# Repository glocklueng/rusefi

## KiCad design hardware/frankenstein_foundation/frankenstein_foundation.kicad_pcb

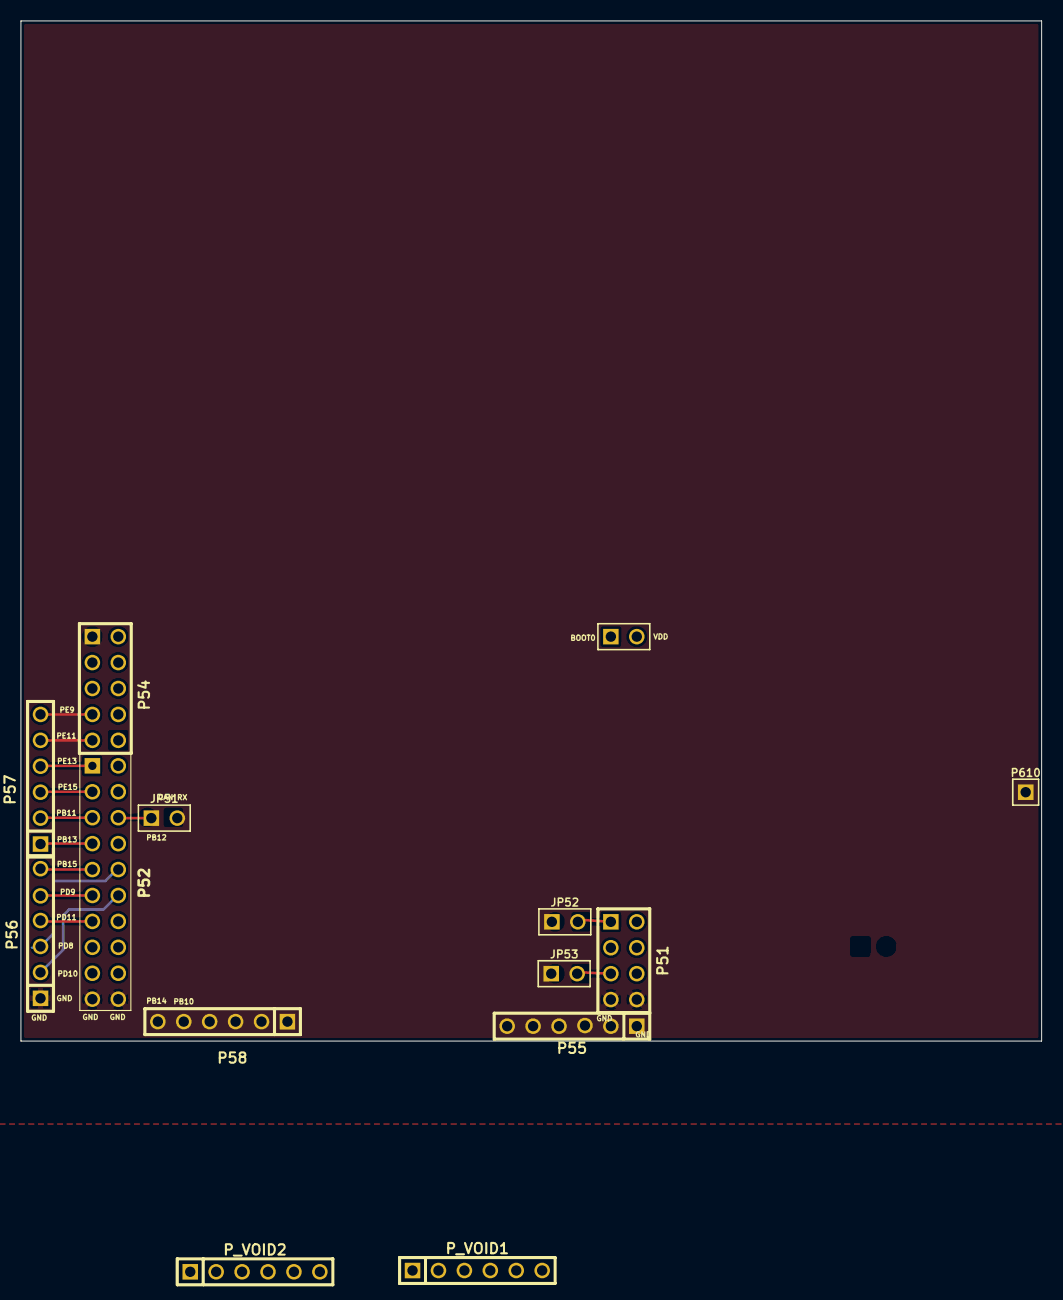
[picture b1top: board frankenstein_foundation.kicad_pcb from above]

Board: 2 copper layers, 100.0 x 99.9 mm, 14 parts (0 on the bottom side), 27 nets.

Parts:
JP51, JP52, JP53: JUMPER; PIN_ARRAY_2_A
P51: CONN_4X2; pin_array_4x2
P52: CONN_10X2; PIN_ARRAY_10X2_M
P53: CONN_2; PIN_ARRAY_2X1
P54: CONN_5X2; PIN_ARRAY_5x2
P55, P56, P57, P58: CONN_6; PIN_ARRAY-6X1
P610: CONN_1; PIN_ARRAY_1
P_VOID1, P_VOID2: CONN_6; PIN_ARRAY-6X1

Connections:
/CAM: JP53.1, P_VOID1.6
/CAN_RX: JP51.2, P_VOID1.5
/CRANK: JP52.1, P_VOID1.4
/H_IN1: P54.8, P_VOID2.6
/H_IN2: P54.10, P_VOID2.5
/H_IN3: P54.6, P_VOID2.3
/H_IN4: P52.2, P_VOID2.4
/H_IN5: P51.6, P55.2
/H_IN6: P51.4, P55.3
/PA8: JP52.2, P51.1
/PB10: P52.4, P58.5
/PB11: P52.5, P57.2
/PB12: JP51.1, P52.6
/PB13: P52.7, P57.1
/PB14: P52.8, P58.6
/PB15: P52.9, P56.6
/PC6: JP53.2, P51.5
/PD8: P52.10, P56.3
/PD9: P52.11, P56.5
/PD10: P52.12, P56.2
/PD11: P52.13, P56.4
/PE9: P54.7, P57.6
/PE11: P54.9, P57.5
/PE13: P52.1, P57.4
/PE15: P52.3, P57.3
/VP: P610.1, P_VOID1.3
GND: P51.7, P51.8, P52.19, P52.20, P55.1, P55.4, P55.5, P55.6, P56.1, P58.1, P58.2, P58.3, P58.4

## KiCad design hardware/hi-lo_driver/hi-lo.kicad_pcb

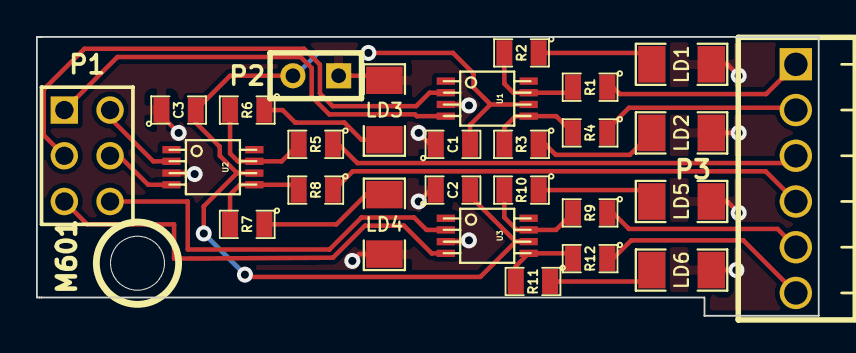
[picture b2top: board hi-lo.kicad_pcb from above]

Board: 2 copper layers, 43.4 x 15.5 mm, 29 parts (1 on the bottom side), 26 nets.

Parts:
C1, C2, C3: 0.1uF; SM0805
G1: LOGO
LD1, LD2, LD3, LD4, LD5, LD6: LED; SM1206
M601: CONN_1; 1pin
P1: CONN_3X2; pin_array_3x2
P2: CONN_2; SIL-2
P3: CONN_6; OSTVN06A150
R1, R4, R5, R8, R9, R12: 100; SM0805
R2, R3, R6, R7, R10, R11: 2700; SM0805
U1, U2, U3: TC4427AVOA; msoic-8

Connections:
/HL1: P3.1, R1.1
/HL2: P3.2, R4.1
/HL3: P3.3, R5.1
/HL4: P3.4, R8.1
/HL5: P3.5, R9.1
/HL6: P3.6, R12.1
/H_IN1: P1.1, U1.4
/H_IN2: P1.2, U2.2
/H_IN3: P1.3, U1.2
/H_IN4: P1.4, U2.4
/H_IN5: P1.5, U3.4
/H_IN6: P1.6, U3.2
/VP: C1.2, C2.2, C3.2, P2.2, U1.6, U2.6, U3.6
GND: C1.1, C2.1, C3.1, LD1.2, LD2.2, LD3.2, LD4.2, LD5.2, LD6.2, P2.1, U1.3, U2.3, U3.3
unnamed: LD5.1, R10.1
unnamed: LD2.1, R3.1
unnamed: R3.2, R4.2, U1.5
unnamed: R7.2, R8.2, U2.5
unnamed: LD3.1, R6.1
unnamed: R5.2, R6.2, U2.7
unnamed: LD1.1, R2.1
unnamed: R1.2, R2.2, U1.7
unnamed: LD4.1, R7.1
unnamed: LD6.1, R11.1
unnamed: R9.2, R10.2, U3.7
unnamed: R11.2, R12.2, U3.5

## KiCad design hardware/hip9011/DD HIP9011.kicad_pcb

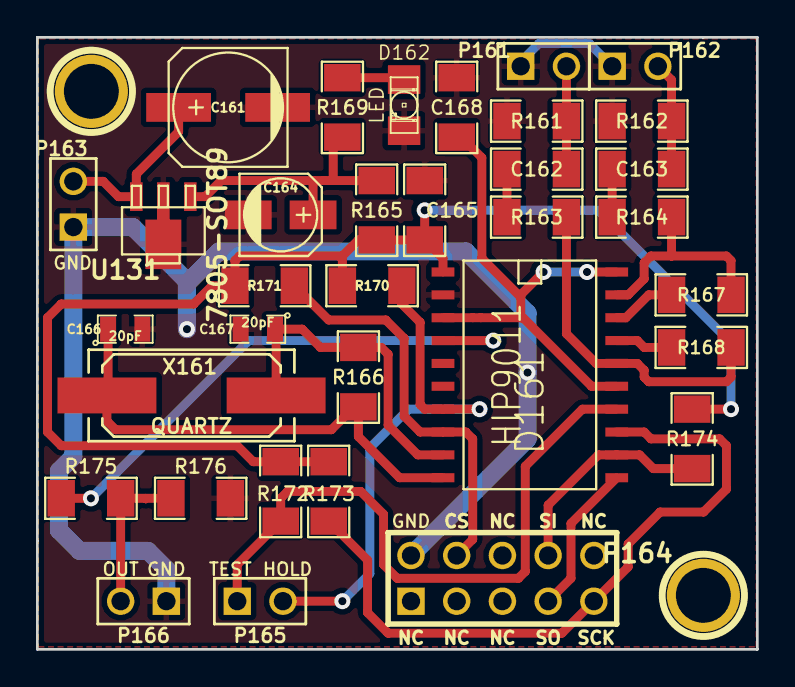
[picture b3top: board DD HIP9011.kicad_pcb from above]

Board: 2 copper layers, 40.0 x 34.0 mm, 35 parts (1 on the bottom side), 24 nets.

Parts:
C161: 100u; c_elec_6.3x5.3
C162, C163: 47n; SM1206
C164: 10u; c_elec_4x5.3
C165: 100n; SM1206
C166, C167: 20pF; SM0805
C168: 22n; SM1206
D161: HIP9011; SO20L
D162: LED; LED-1206
G161: LOGO; LOGO_F
P161: KNOCK 1; PIN_ARRAY_2X1
P162: KNOCK 2; PIN_ARRAY_2X1
P163: 12V; PIN_ARRAY_2X1
P164: CONN_5X2; PIN_ARRAY_5x2
P165, P166: CONN_2; PIN_ARRAY_2X1
R161, R162, R166: 1M; SM1206
R163, R164, R175, R176: 10k; SM1206
R165: 10R; SM1206
R167, R168: 68k; SM1206
R169: 470R; SM1206
R170, R171, R172, R173, R174: 1K; SM1206
U131: 7805-SOT89; sot89
X161: QUARTZ; Q_49U3HMS

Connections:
/+5V: C165.1, D161.1, R165.2, R170.1, R171.1, R172.1, R173.1, R174.1
/+12V: C161.1, P163.2, U131.3
/CS: D161.8, P164.4, R171.2
/GND: C161.2, C164.2, C165.2, C166.2, C167.2, C168.2, D161.2, D162.2, P161.1, P162.1, P163.1, P164.2, P166.1, R161.2, R162.2, R176.2, U131.2
/INT/HLD: D161.7, P165.2, R170.2
/INTOUT: D161.4, R175.1
/OUT: P166.2, R175.2, R176.1
/SCK: D161.13, P164.9, R173.2
/SI: D161.12, P164.8, R174.2
/SO: D161.11, P164.7
/TEST: D161.14, P165.1, R172.2
unnamed: D162.1, R169.1
unnamed: C164.1, R165.1, R169.2, U131.1
unnamed: C167.1, D161.9, R166.2, X161.2
unnamed: C163.1, P162.2, R162.1
unnamed: C163.2, R164.1
unnamed: C166.1, D161.10, R166.1, X161.1
unnamed: C168.1, D161.3, D161.15, D161.20
unnamed: D161.16, R163.2, R168.2
unnamed: D161.17, R168.1
unnamed: D161.18, R167.1
unnamed: D161.19, R164.2, R167.2
unnamed: C162.2, R163.1
unnamed: C162.1, P161.2, R161.1

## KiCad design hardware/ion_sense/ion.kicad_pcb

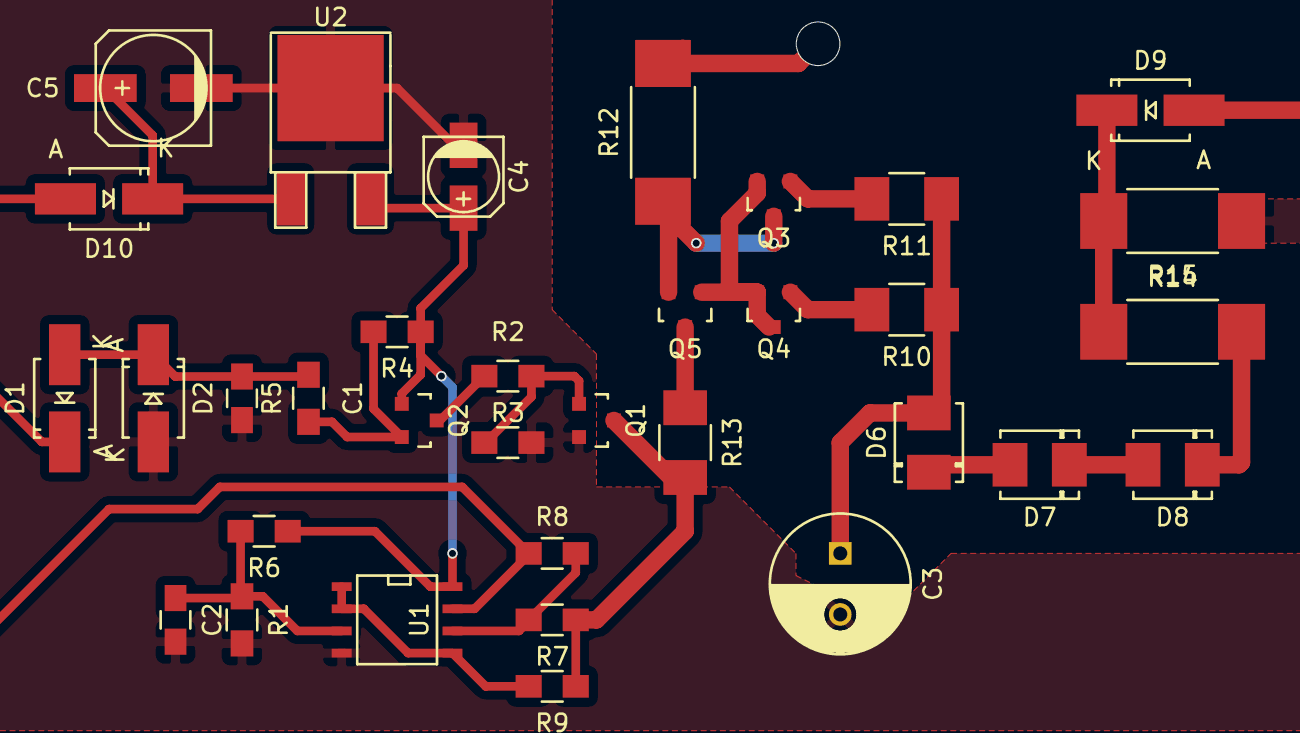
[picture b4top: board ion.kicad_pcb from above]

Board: 2 copper layers, 40 parts (0 on the bottom side), 25 nets.

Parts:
C1: 0.1uF; C_0805_HandSoldering
C2: 1uF; C_0805_HandSoldering
C3: 2.2uF 350V; C_Radial_D8_L11.5_P3.5
C4: 4.7uF 16V; c_elec_4x4.5
C5: 47uF 25V; c_elec_6.3x4.5
D1, D2, D9, D10: US1M; SMA_Handsoldering
D6, D7, D8: 1N4740A; DO-214BA
P0, P1, P2, P3, P4, P5: CONN_01X01; MountingHole_2-5mm
Q1: MMBT3904; SOT-23
Q2, Q3, Q4, Q5: MPSA92; SOT-23
R1, R6, R7, R8: 51k; R_0805_HandSoldering
R2: 2k; R_0805_HandSoldering
R3: 3.9k; R_0805_HandSoldering
R4: 10k; R_0805_HandSoldering
R5: 1k; R_0805_HandSoldering
R9: 4.7k; R_0805_HandSoldering
R10, R11: 560; R_1210_HandSoldering
R12: 180k; R_2512_HandSoldering
R13: 68k; R_1210_HandSoldering
R14: 33k; R_2512_HandSoldering
R15: 1M; R_2512_HandSoldering
U1: LM2904; SOIC-8-N
U2: MC78M05CDT; TO-252-2Lead

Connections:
Earth: C1.2, C2.2, C3.2, C4.2, C5.2, D2.2, P5.1, Q1.2, R1.2, R2.2, R15.1, U1.4, U2.2
unnamed: C1.1, D1.2, D2.1, R5.2
unnamed: C2.1, R1.1, R6.2, U1.3
unnamed: C3.1, D6.2, R10.1, R11.1
unnamed: C4.1, Q2.1, R4.1, R6.1, U1.8, U2.3
unnamed: C5.1, D10.1, U2.1
unnamed: D1.1, P0.1
unnamed: D6.1, D7.2
unnamed: D7.1, D8.2
unnamed: D8.1, R14.2
unnamed: D9.1, R14.1, R15.2
unnamed: D9.2, P4.1
unnamed: D10.2, P1.1
unnamed: P3.1, R8.1, U1.7
unnamed: Q1.1, R2.1, R3.1
unnamed: Q1.3, R7.1, R9.1, R13.2
unnamed: Q2.2, R4.2, R5.1
unnamed: Q2.3, R3.2
unnamed: Q3.1, R11.2
unnamed: Q3.2, Q4.2, Q4.3, Q5.1
unnamed: Q3.3, Q5.2, R12.1
unnamed: Q4.1, R10.2
unnamed: Q5.3, R13.1
unnamed: R7.2, R8.2, U1.6
unnamed: R9.2, U1.1, U1.2, U1.5

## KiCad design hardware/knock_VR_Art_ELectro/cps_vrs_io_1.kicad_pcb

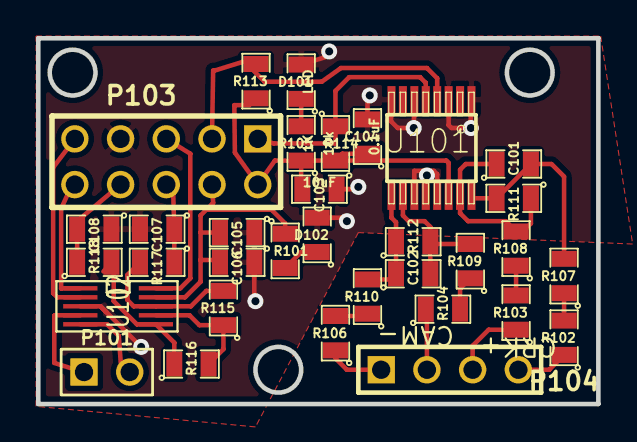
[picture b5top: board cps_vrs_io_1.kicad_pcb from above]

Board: 2 copper layers, 31.1 x 20.3 mm, 34 parts (1 on the bottom side), 29 nets.

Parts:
C101, C102, C108: 1000pF; SM0805
C103: 10uF; SM0805
C104, C106, C107: 0.1uF; SM0805
C105: 1uF; SM0805
D101, D102: LED; SM0805
G101: LOGO; LOGO_F
P101: CONN_2; PIN_ARRAY_2_A
P103: CONN_5X2; PIN_ARRAY_5x2
P104: CONN_4; PIN_ARRAY_4x1
R101, R105: 1K; SM0805
R102, R103, R104, R106, R107, R108, R109, R110, R111, R112: 5k; SM0805
R113, R114: 10k; SM0805
R115, R116: 10K; SM0805
R117, R118: 20K; SM0805
U101: MAX9926/9927; maxim-10-QSOP16
U102: MAX9939; uMAX-uSOP_10

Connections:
/5V: C103.2, C104.1, P103.2, R105.1, R113.1, R114.2, U101.14
/5v stab: C105.2, C106.2, P103.4, R101.1, U102.9
/CAM: P103.1, R114.1, U101.5
/CAM+: P104.1, R106.1
/CAM-: P104.2, R104.1
/CRANK: P103.3, R113.2, U101.4
/CRK2+: P104.4, R102.1
/CRK2-: P104.3, R103.1
/CS-KN1: P103.5, U102.10
/MISO: P103.9, U102.2
/SCK: P103.10, U102.1
/knock1+: C107.1, P103.6, R117.1
/knock1-: C108.2, P103.8, R118.1
/knock_1+p: P101.2, U102.5
/knock_1-p: P101.1, U102.4
GND: C103.1, C104.2, C105.1, C106.1, C107.2, C108.1, D101.2, D102.2, P103.7, U101.1, U101.3, U101.6, U101.8, U101.11, U101.12, U101.13, U102.3
unnamed: R115.1, R116.2, U102.7
unnamed: R115.2, R117.2, U102.8
unnamed: R116.1, R118.2, U102.6
unnamed: D101.1, R105.2
unnamed: D102.1, R101.2
unnamed: R102.2, R107.1
unnamed: R104.2, R109.1
unnamed: R106.2, R110.1
unnamed: R103.2, R108.1
unnamed: C101.1, R108.2, R111.1, U101.15
unnamed: C101.2, R107.2, R111.2, U101.16
unnamed: C102.1, R110.2, R112.1, U101.9
unnamed: C102.2, R109.2, R112.2, U101.10

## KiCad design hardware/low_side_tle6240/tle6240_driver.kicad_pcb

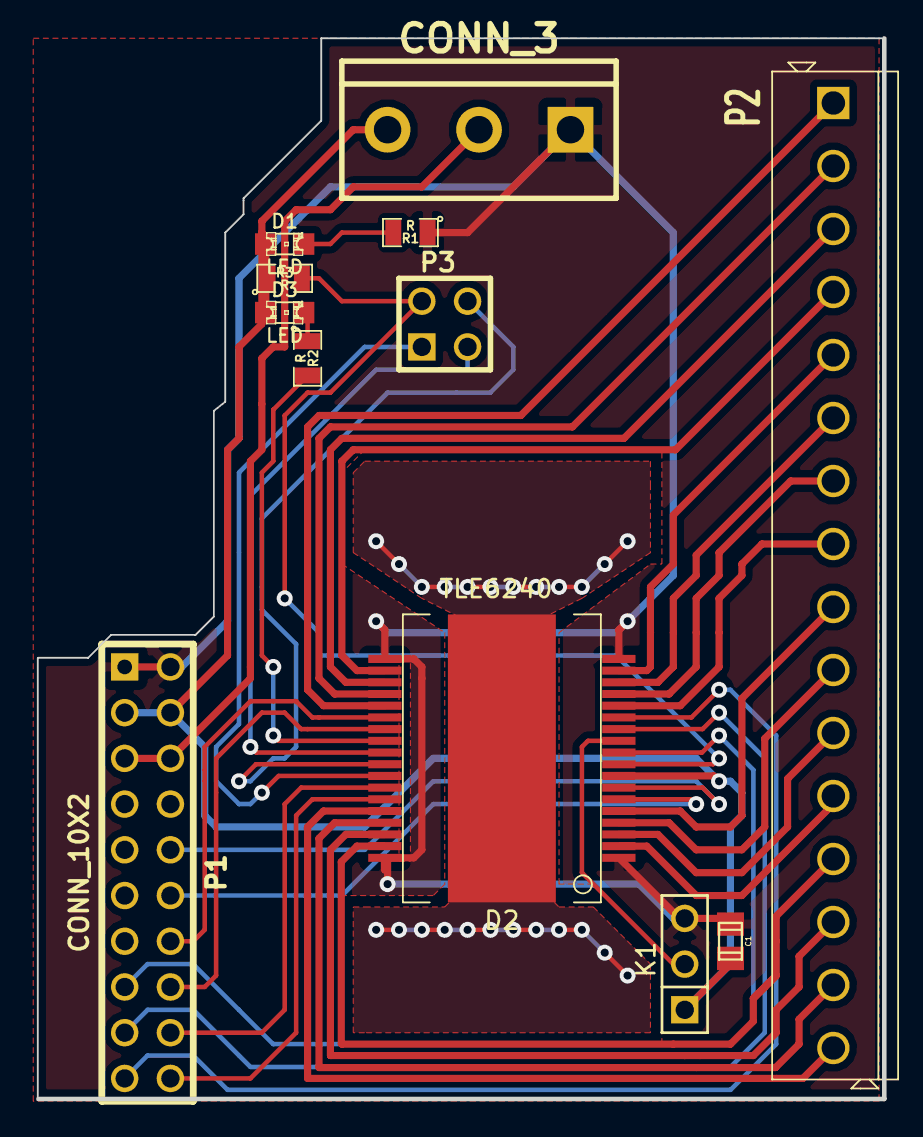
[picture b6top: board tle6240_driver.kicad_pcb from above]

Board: 2 copper layers, 47.0 x 58.9 mm, 12 parts (0 on the bottom side), 36 nets.

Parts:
C1: C; c_0805
D1, D3: LED; LED-0805
D2: TLE6240; PG-DSO-36
K1: CONN_3; PIN_ARRAY_3X1
K2: CONN_3; bornier3
P1: CONN_10X2; PIN_ARRAY_10X2
P2: CONN_16; SIL-16_3.5MM
P3: CONN_2X2; PIN_ARRAY_2X2
R1, R2, R3: R; SM0805

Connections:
+5V: C1.1, D1.1, D2.8, D3.1, K1.1, K2.3, P1.3, P1.4, R3.1
/+3.3V: K2.2, P1.5, P1.6
/CS: D2.10, P1.15
/Fault: D2.26, R2.2
/IN1: D2.6, P1.12
/IN2: D2.7, P1.10
/IN3: D2.12, P1.17
/IN4: D2.13, P1.19
/IN9: D2.24, P1.14
/IN10: D2.25, P1.16
/IN11: D2.30, P1.18
/IN12: D2.31, P1.20
/OUT1: D2.4, P2.10
/OUT2: D2.5, P2.9
/OUT3: D2.14, P2.8
/OUT4: D2.15, P2.7
/OUT5: D2.22, P2.2
/OUT6: D2.23, P2.1
/OUT7: D2.32, P2.16
/OUT8: D2.33, P2.15
/OUT9: D2.2, P2.12
/OUT10: D2.3, P2.11
/OUT11: D2.16, P2.6
/OUT12: D2.17, P2.5
/OUT13: D2.20, P2.4
/OUT14: D2.21, P2.3
/OUT15: D2.34, P2.14
/OUT16: D2.35, P2.13
/PRG: D2.11, K1.2
/Reset: D2.9, P3.2, R3.2
/SCLK: D2.28, P3.4
/SI: D2.29, P3.1
/SO: D2.27, P3.3
GND: C1.2, D2.1, D2.18, D2.19, D2.36, K1.3, K2.1, P1.1, P1.2, R1.1
unnamed: D3.2, R2.1
unnamed: D1.2, R1.2

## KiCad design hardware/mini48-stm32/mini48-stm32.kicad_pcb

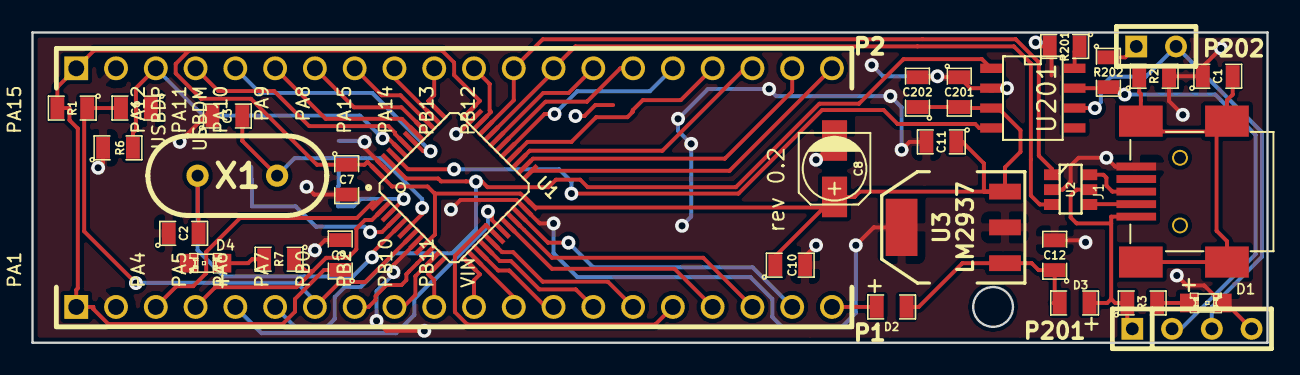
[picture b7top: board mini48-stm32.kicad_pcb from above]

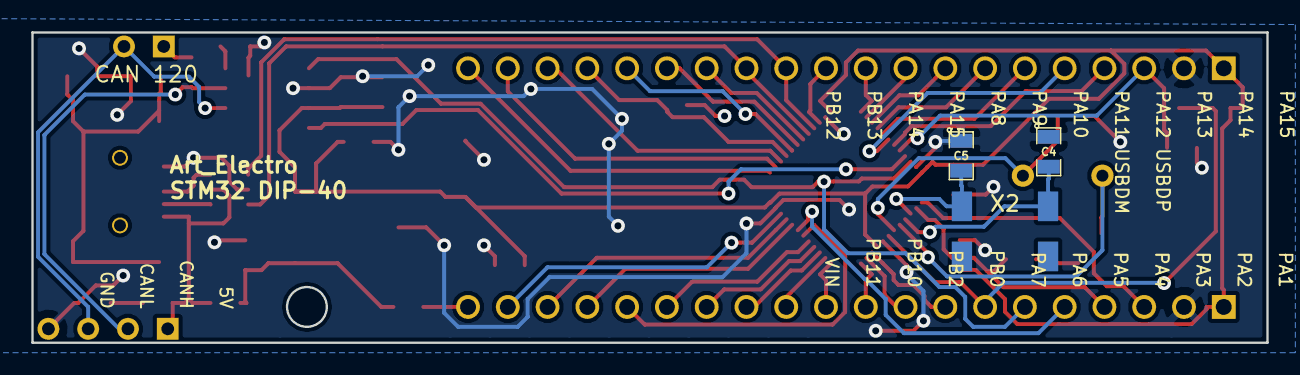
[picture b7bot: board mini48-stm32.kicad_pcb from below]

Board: 2 copper layers, 78.9 x 19.8 mm, 36 parts (3 on the bottom side), 54 nets.

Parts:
C1: 4700pF; SM0805
C2, C3, C4, C5: 18pF; SM0805
C6: 100nF; SM0805
C7, C10, C11: 1uF; SM0805
C8: 47uF; CP_elec_4x5.3
C9, C201: 0.1uF; SM0805
C12: 10uF; SM0805
C202: 4.7uF; SM0805
D1: GREEN; LED-0805_A
D2, D3: DIODESCH; SM0805-diode
D4: BLUE; LED-0805_A
J1: MINI-USB; MINI-USB-5P-3400020P1
P1, P2: CONN_20; PIN_ARRAY_20X1
P201: CONN_4; SIL-4
P202: JUMPER; JUMPER-2
R1, R3, R7: 1k; SM0805
R2: 1M; SM0805
R6, R201: 10k; SM0805
R202: 120; SM0805
U1: STM32F103C8; lqfp48
U2: NUF2101MT1G; SOT-457
U3: LM2937; SOT223
U201: SN65HVD230; SO8E
X1: 8MHz; HC-49V
X2: 32768KHz; MC-306

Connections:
/BOOT0: P2.3, R6.2, U1.44
/CAN BUS/3.3V: C7.1, C8.1, C9.1, C10.1, C11.1, C201.2, C202.1, P1.1, P2.1, R1.2, U1.9, U1.24, U1.36, U1.48, U3.3, U201.3
/CAN BUS/5V: D3.1, J1.1, P201.1, R3.1, U2.5
/CAN BUS/CANH: P201.2, R202.2, U201.7
/CAN BUS/CANL: P201.3, P202.2, U201.6
/CAN BUS/CAN_RX: U1.45, U201.4
/CAN BUS/CAN_TX: P1.6, U1.46, U201.1
/D+: J1.3, U2.6
/D-: J1.2, U2.4
/PA0: P1.8, U1.10
/PA1: P1.9, U1.11
/PA2: P1.10, U1.12
/PA3: P1.11, U1.13
/PA4: P1.12, U1.14
/PA5: P1.13, U1.15
/PA6: P1.14, U1.16
/PA7: P1.15, U1.17
/PA8: P2.16, U1.29
/PA9: P2.15, U1.30
/PA10: P2.14, U1.31
/PA11_USBDM: P2.13, U1.32, U2.3
/PA12_USBDP: P2.12, U1.33, U2.1
/PA13: P2.11, U1.34
/PA14: P2.10, U1.37
/PA15: P2.9, U1.38
/PB0: P1.16, U1.18
/PB1: P1.5, U1.19
/PB2: P1.17, U1.20
/PB3: P2.8, U1.39
/PB4: P2.7, U1.40
/PB5: P2.6, U1.41
/PB6: P2.5, U1.42
/PB7: P2.4, U1.43
/PB10: P1.18, U1.21
/PB11: P1.19, U1.22
/PB12: P2.20, U1.25
/PB13: P2.19, U1.26
/PB14: P2.18, U1.27
/PB15: P2.17, U1.28
/PC13: P1.4, R7.1, U1.2
/PC14_OSC32_IN: C5.2, U1.3, X2.2
/PC15_OSC32_OUT: C4.2, U1.4, X2.1
/PD0: C2.2, U1.5, X1.1
/PD1: C3.2, U1.6, X1.2
/Reset: C6.2, P1.7, R1.1, U1.7
/VBAT: P1.3, U1.1
/VIN: D2.1, P1.20
GND: C1.1, C2.1, C3.1, C4.1, C5.1, C6.1, C7.2, C8.2, C9.2, C10.2, C11.2, C12.2, C201.1, C202.2, D1.2, D4.2, J1.5, P1.2, P2.2, P201.4, R2.2, R6.1, R201.2, U1.8, U1.23, U1.35, U1.47, U2.2, U3.2, U3.4, U201.2
unnamed: C12.1, D2.2, D3.2, U3.1
unnamed: D4.1, R7.2
unnamed: D1.1, R3.2
unnamed: C1.2, J1.6, R2.1
unnamed: P202.1, R202.1
unnamed: R201.1, U201.8
